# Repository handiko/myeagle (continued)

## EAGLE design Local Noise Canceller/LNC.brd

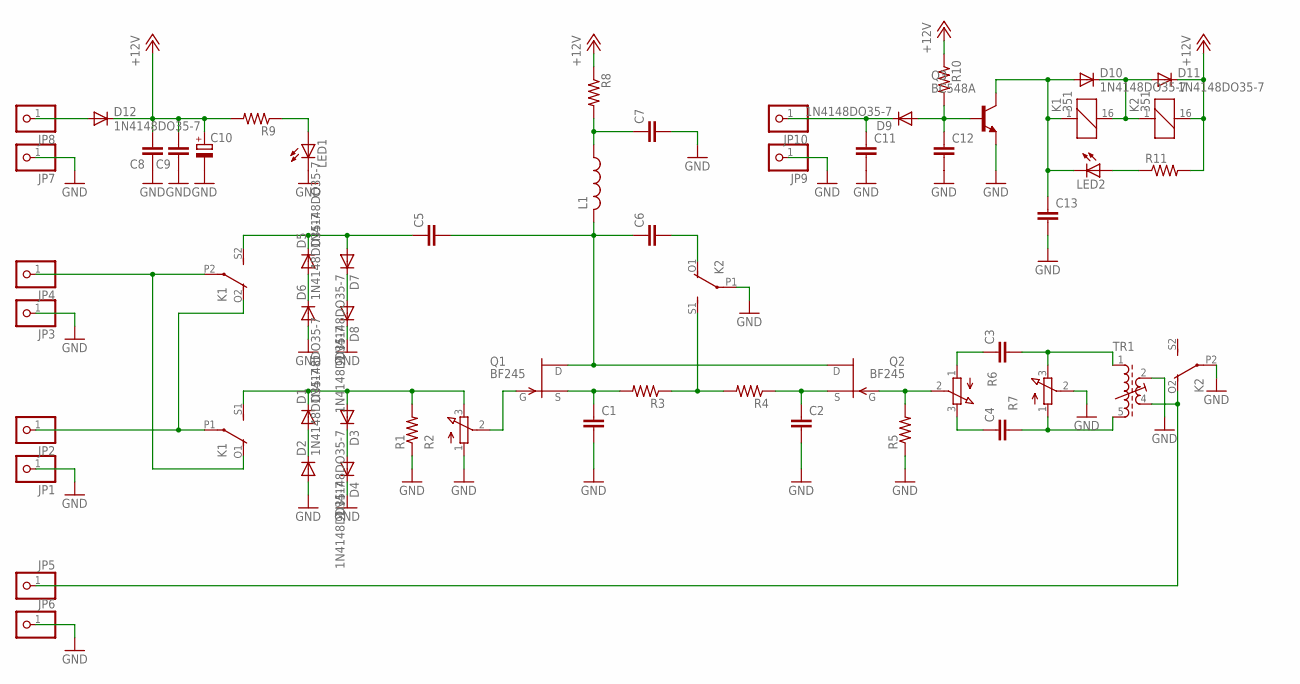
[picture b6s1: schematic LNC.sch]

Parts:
C1, C2, C3, C4, C5, C6, C7, C8, C9, C11, C12, C13: C-EU050-030X075; C050-030X075
C10: CPOL-EUE2.5-7; E2,5-7
D1, D2, D3, D4, D5, D6, D7, D8, D9, D10, D11, D12: 1N4148DO35-7; DO35-7
JP1, JP2, JP3, JP4, JP5, JP6, JP7, JP8, JP9, JP10: PINHD-1X1; 1X01
K1, K2: 351
L1: L-US0207/10; 0207/10
LED1, LED2: LED3MM
Q1, Q2: BF245; TO92
Q3: BC548A; TO92-EBC
R1, R3, R4, R5, R8, R9, R10, R11: R-US_0204/7; 0204/7
R2, R6, R7: 3RP/1610N
TR1: 71-4-1542; 71-5

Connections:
+12V: C8.2, C9.2, C10.+, D11.C, D12.C, K2.16 (2), R8.1, R9.2, R10.1, R11.2
GND: C1.2, C2.2, C7.2, C8.1, C9.1, C10.-, C11.2, C12.2, C13.2, D2.A, D4.C, D6.A, D8.C, JP1.1, JP3.1, JP6.1, JP7.1, JP9.1, K2.P1, K2.P2, LED1.K (C), Q3.E, R1.1, R2.1 (A), R5.1, R7.2 (S), TR1.2 (A2)
unnamed: JP4.1, K1.O1 (O), K1.P2
unnamed: JP2.1, K1.O2 (O), K1.P1
unnamed: Q1.3 (G), R2.2 (S)
unnamed: C2.1, Q2.2 (S), R4.1
unnamed: C5.1, D5.C, D7.A, K1.S2 (S)
unnamed: D1.C, D3.A, K1.S1 (S), R1.2, R2.3 (E)
unnamed: K2.S1 (S), R3.1, R4.2
unnamed: D1.A, D2.C
unnamed: D3.C, D4.A
unnamed: C1.1, Q1.2 (S), R3.2
unnamed: Q2.3 (G), R5.2, R6.2 (S)
unnamed: C3.1, R6.1 (A)
unnamed: D5.A, D6.C
unnamed: D7.C, D8.A
unnamed: C3.2, R7.3 (E), TR1.1 (A1)
unnamed: C4.2, R7.1 (A), TR1.5 (E1)
unnamed: C4.1, R6.3 (E)
unnamed: C5.2, C6.1, L1.2, Q1.1 (D), Q2.1 (D)
unnamed: C6.2, K2.O1 (O)
unnamed: JP5.1, K2.O2 (O), TR1.4 (E2)
unnamed: D10.C, D11.A, K1.16 (2), K2.1
unnamed: C7.1, L1.1, R8.2
unnamed: LED1.A, R9.1
unnamed: C12.1, D9.A, Q3.B, R10.2
unnamed: C13.1, D10.A, K1.1, LED2.K (C), Q3.C
unnamed: LED2.A, R11.1
unnamed: C11.1, D9.C, JP10.1
unnamed: D12.A, JP8.1

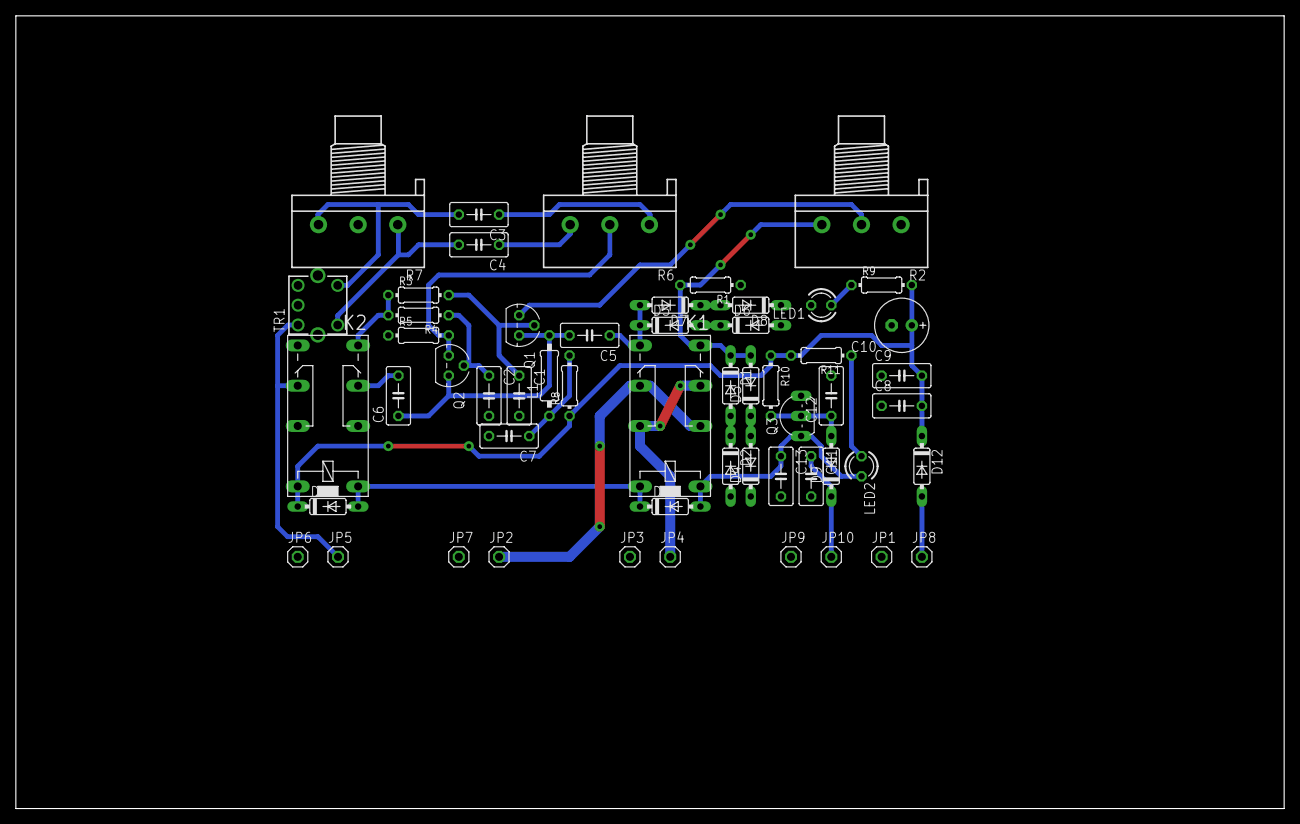
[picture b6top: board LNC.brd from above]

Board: 2 copper layers, 160.0 x 100.0 mm, 55 parts (0 on the bottom side), 30 nets.

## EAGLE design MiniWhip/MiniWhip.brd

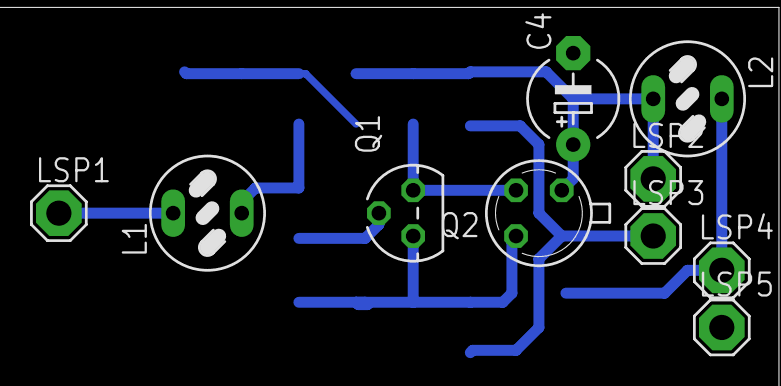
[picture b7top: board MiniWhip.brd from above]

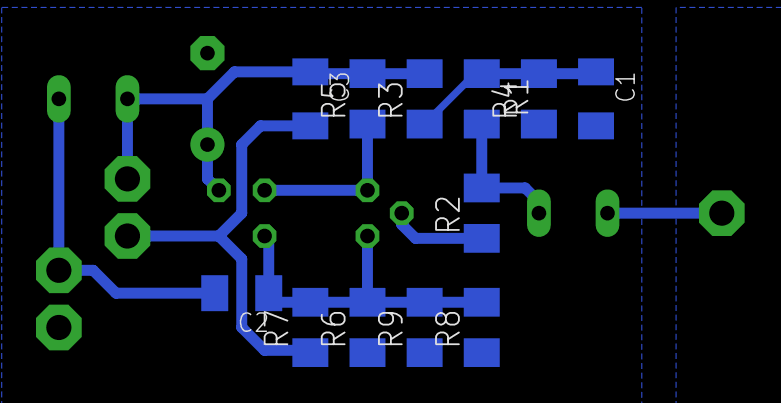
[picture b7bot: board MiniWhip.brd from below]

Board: 2 copper layers, 22 parts (12 on the bottom side), 9 nets.

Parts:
C1, C2, C3: C1206K
C4: E5-5
L1, L2: 82114R
LSP1, LSP2, LSP3, LSP4, LSP5: SE14
Q1: 2N3819; TO92F
Q2: 2N2907; TO18
R1, R2, R3, R4, R5, R6, R7, R8, R9: M1206

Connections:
ANT: L1.1, LSP1.MP
GND: C1.2, C3.2, C4.-, LSP3.MP, LSP5.MP, R4.1, R6.1, R7.1, R8.1, R9.1
unnamed: L1.2, R1.2, R2.2
unnamed: C1.1, R1.1, R3.1, R4.2
unnamed: Q1.G, R2.1
unnamed: Q1.D, Q2.2, R5.1
unnamed: C2.1, Q1.S, Q2.3, R6.2, R7.2, R8.2, R9.2
unnamed: C2.2, L2.1, LSP4.MP
VCC: C3.1, C4.+, L2.2, LSP2.MP, Q2.1, R3.2, R5.2

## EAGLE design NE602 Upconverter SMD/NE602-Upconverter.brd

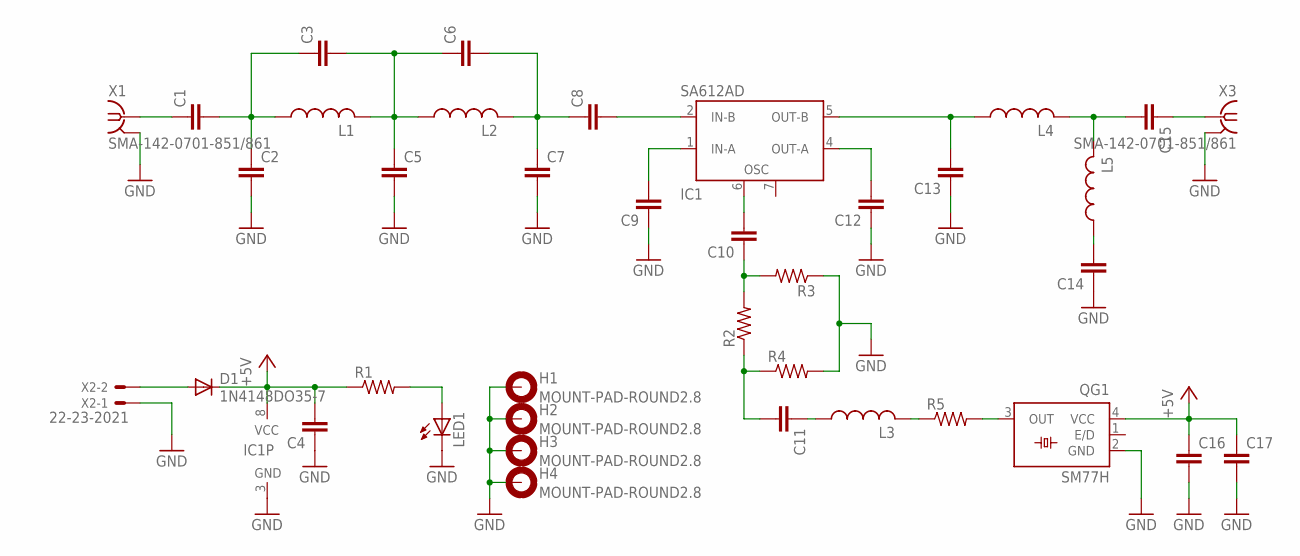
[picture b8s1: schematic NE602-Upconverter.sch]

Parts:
C1, C2, C3, C4, C5, C6, C7, C8, C9, C10, C11, C12, C13, C14, C15, C16, C17: C-EUC1206; C1206
D1: 1N4148DO35-7; DO35-7
H1, H2, H3, H4: MOUNT-PAD-ROUND2.8; 2,8-PAD
IC1: SA612AD; SO08
L1, L2, L3, L4, L5: L-USL3225M; L3225M
LED1: LED3MM
QG1: SM77H
R1, R2, R3, R4, R5: R-US_M1206; M1206
X1, X3: SMA-142-0701-851/861; J502-ND-142-0701-851/861
X2: 22-23-2021

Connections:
+5V: C4.2, C16.1, C17.1, D1.C, IC1.8 (VCC), QG1.4 (VCC), R1.1
GND: C2.2, C4.1, C5.2, C7.2, C9.1, C12.1, C13.1, C14.1, C16.2, C17.2, H1.B2,8, H2.B2,8, H3.B2,8, H4.B2,8, IC1.3 (GND), LED1.K (C), QG1.2 (GND), R3.1, R4.2, X1.G@1 (2), X1.G@2 (2), X1.G@3 (2), X1.G@4 (2), X2.1, X3.G@1 (2), X3.G@2 (2), X3.G@3 (2), X3.G@4 (2)
unnamed: C1.2, C2.1, C3.1, L1.1
unnamed: C3.2, C5.1, C6.1, L1.2, L2.1
unnamed: C6.2, C7.1, C8.1, L2.2
unnamed: C8.2, IC1.2 (IN-B)
unnamed: C9.2, IC1.1 (IN-A)
unnamed: C10.2, IC1.6 (OSC)
unnamed: C14.2, L5.1
unnamed: C13.2, IC1.5 (OUT-B), L4.1
unnamed: C15.2, L4.2, L5.2
unnamed: C12.2, IC1.4 (OUT-A)
unnamed: C11.2, R2.1, R4.1
unnamed: C10.1, R2.2, R3.2
unnamed: C11.1, L3.1
unnamed: LED1.A, R1.2
unnamed: L3.2, R5.1
unnamed: QG1.3 (OUT), R5.2
unnamed: C1.1, X1.1
unnamed: C15.1, X3.1
unnamed: D1.A, X2.2

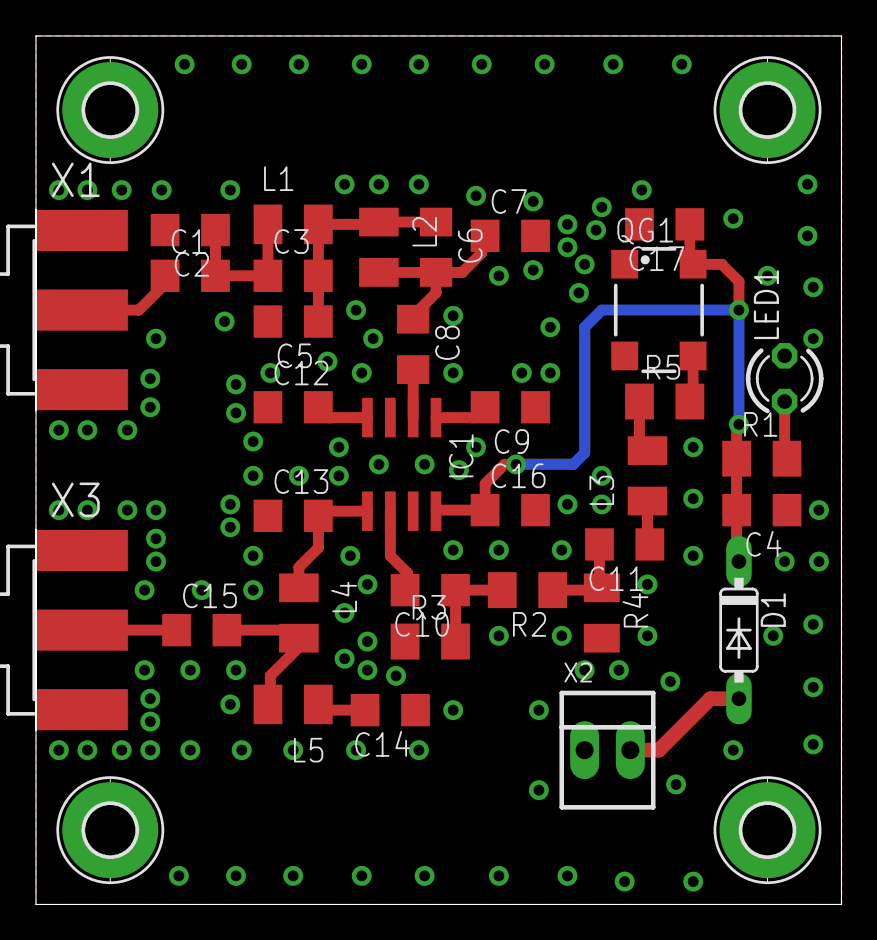
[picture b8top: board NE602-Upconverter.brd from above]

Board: 2 copper layers, 44.7 x 48.2 mm, 38 parts (0 on the bottom side), 21 nets.
